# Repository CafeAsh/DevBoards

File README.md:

# Embedded Hardware Design Library

A collection of reusable embedded hardware designs developed as a personal reference library for future electronics and embedded-systems projects.

This repository contains custom development boards, microcontroller platforms, and DC-DC power-conversion designs. The goal is to maintain a structured library of proven circuit designs that can be reused, adapted, and expanded for future projects.

The designs emphasize **practical PCB implementation, component selection, power integrity, signal integrity, manufacturability, and reusable hardware architecture**.

This repository also serves as an ongoing engineering and learning platform. Designs are developed, evaluated, and refined to strengthen practical skills in embedded systems, PCB design, power electronics, signal integrity, and hardware validation. Lessons learned from each design are incorporated into subsequent revisions and projects.

---

## Repository Contents

### Microcontroller Development Boards

| Platform      | MCU                              | Primary Focus                                              |
| ------------- | -------------------------------- | ---------------------------------------------------------- |
| ATtiny1616    | Microchip ATtiny1616             | Low-cost / low-power embedded control                      |
| ATmega32U4    | Microchip ATmega32U4             | USB-capable embedded applications                          |
| ESP32-S3      | Espressif ESP32-S3               | Wi-Fi / Bluetooth / high-performance embedded applications |
| RP2040        | Raspberry Pi RP2040              | Dual-core MCU development                                  |
| STM32F103C8T6 | STMicroelectronics STM32F103C8T6 | ARM Cortex-M3 embedded development                         |

### Power Electronics

The repository also contains several DC-DC converter reference designs:

* Buck converter
* Boost converter
* SEPIC converter

These designs are intended as reusable starting points for future power-supply requirements, with component values and operating parameters selected for their respective target applications.

---

## Design Philosophy

The primary objective of this repository is **reusability**.

Rather than designing every development board or power stage from scratch, commonly used circuits are maintained as modular reference designs that can be incorporated into future projects.

Designs are developed with consideration for:

* Component availability
* PCB manufacturability
* Power distribution
* Decoupling and bypassing
* Signal integrity
* Grounding and return paths
* Programming and debugging interfaces
* Protection circuitry
* Ease of modification and reuse

---

## Development Boards

### ATtiny1616

Reference development board centered around the Microchip ATtiny1616 microcontroller.

Design considerations include:

* USB-to-serial conversion
* Programming/debug interface
* GPIO accessibility
* External power input
* Reset/programming provisions

### ATmega32U4

USB-capable development board based on the ATmega32U4.

The design provides a reusable platform for projects requiring:

* Native USB
* GPIO expansion
* Embedded control
* HID applications
* External peripherals

### ESP32-S3

Development platform based on the ESP32-S3 for projects requiring greater processing capability and wireless connectivity.

The design focuses on providing a reusable hardware platform while accounting for the additional power, RF, and high-speed considerations associated with the device.

### RP2040

Development board based on the Raspberry Pi RP2040.

The design provides a flexible platform for embedded applications requiring:

* Dual-core processing
* High-speed GPIO
* Programmable I/O
* USB connectivity
* External peripheral interfaces

### STM32F103C8T6

ARM Cortex-M3 development platform based on the STM32F103C8T6.

The design provides a compact reference platform for applications requiring:

* ARM Cortex-M development
* General-purpose peripherals
* Multiple communication interfaces
* External debugging/programming

---

## Power Conversion

### Buck Converter

Step-down DC-DC converter designs for applications requiring a regulated output voltage below the input voltage.

Design considerations include:

* Switching frequency
* Inductor selection
* Output capacitance
* MOSFET selection
* Diode or synchronous rectification
* Feedback network
* Switching losses
* Thermal performance
* PCB current paths

### Boost Converter

Step-up DC-DC converter designs for generating an output voltage greater than the input voltage.

Key considerations include:

* Inductor selection
* Switching device selection
* Diode characteristics
* Output ripple
* Duty-cycle limitations
* Feedback and regulation
* Current requirements

### SEPIC Converter

Single-Ended Primary-Inductor Converter designs for applications requiring an output voltage that may be either above or below the input voltage.

SEPIC designs are particularly useful when the input voltage can cross the desired output voltage while maintaining a non-inverting regulated output.

---

## Design Documentation

Each design is intended to become increasingly self-documenting as the repository develops.

Where applicable, documentation will include:

* Design objectives
* Electrical specifications
* Schematic
* PCB layout
* Bill of materials
* Component selection rationale
* Design calculations
* Simulation results
* PCB fabrication files
* Assembly information
* Bring-up and validation notes
* Known limitations
* Revision history

Measured results will be distinguished from simulated or calculated values.

---

## Tools

The designs in this repository may utilize:

* **KiCad** — Schematic capture and PCB design
* **LTspice** — Circuit simulation
* **Datasheet analysis** — Component selection and electrical verification
* **Embedded development tools** — Firmware development and hardware bring-up

Additional tools may be added as the library expands.

---

## Future Development

Planned additions and improvements include:

* Additional MCU development boards
* Expanded DC-DC converter library
* Reusable power-entry circuits
* USB interface designs
* Debug/programming interfaces
* ESD and transient protection circuits
* Load-switch and power-management circuits

---

## Status

This repository is an actively evolving engineering reference library.

Designs should be considered **development/reference hardware unless explicitly marked as validated**. Electrical specifications, component selections, and layouts may change as designs are tested and refined.

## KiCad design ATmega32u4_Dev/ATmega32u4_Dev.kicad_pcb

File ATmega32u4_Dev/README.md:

# ATmega32U4 Development Board

Development board based on the **ATmega32U4** microcontroller, designed for USB-enabled embedded projects, rapid prototyping, and firmware experimentation.

## Overview

This project provides a hardware platform built around the ATmega32U4, a microcontroller with native USB support.

Ideal use cases include:

* USB HID devices (keyboards, mice, gamepads)
* Serial communication over USB (CDC)
* Custom USB devices
* General embedded applications

## Features

* ATmega32U4 microcontroller
* Native USB support (no external USB-to-UART chip required)
* On-board 5V voltage regulation
* Power and Dataline surge protection
* ISP programming header
* Power Status LED
* Programable on board LED (Pin 13)
* GPIO breakout pins
* 16MHz Crystal Oscillator
* Designed to fit standard breadboards

## Microcontroller Details

* **Core:** AVR 8-bit
* **Flash Memory:** 32 KB
* **SRAM:** 2.5 KB
* **EEPROM:** 1 KB
* **Clock Speed:**  16 MHz
* **Interfaces:**
  * USB 2.0 Full Speed
  * UART
  * SPI
  * I2C (TWI)

## Pinout

*Pinout leaves some to be desired. Future re-works will better address pin layout*

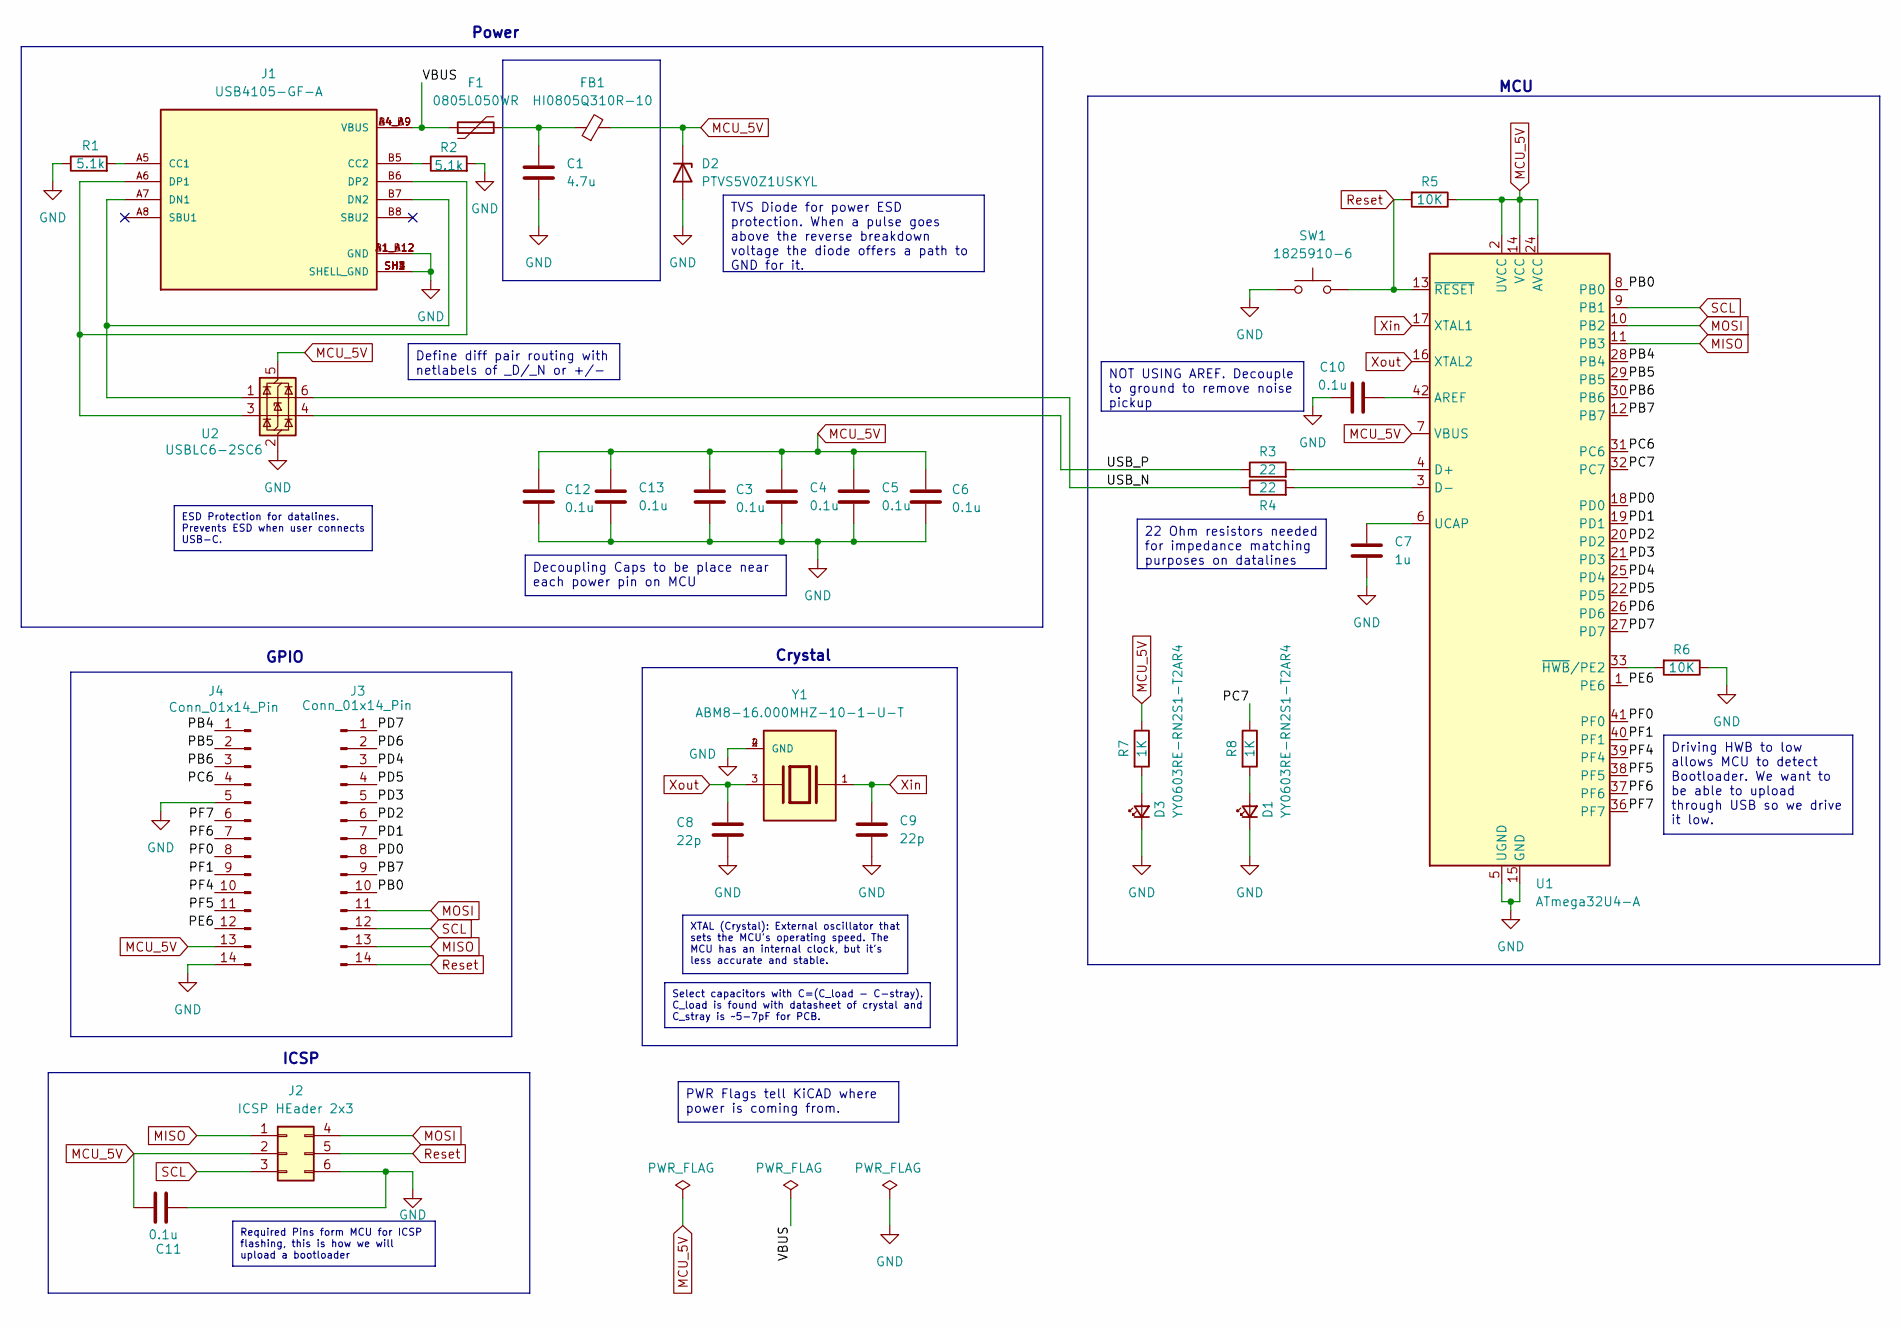
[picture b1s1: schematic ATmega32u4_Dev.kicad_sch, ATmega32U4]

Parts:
C1: 4.7u; C_0402_1005Metric
C3, C4, C5, C6, C10, C11, C12, C13: 0.1u; C_0402_1005Metric
C7: 1u; C_0402_1005Metric
C8, C9: 22p; C_0402_1005Metric
D1, D3: YY0603RE-RN2S1-T2AR4; LED_0603_1608Metric
D2: PTVS5V0Z1USKYL; Nexperia_DSN1608-2_1.6x0.8mm
F1: 0805L050WR; Fuse_0805_2012Metric_Pad1.15x1.40mm_HandSolder
FB1: HI0805Q310R-10; L_0805_2012Metric_Pad1.05x1.20mm_HandSolder
J1: USB4105-GF-A; GCT_USB4105-GF-A; PARTREV B4
J2: ICSP HEader 2x3; 02x03 Header
J3, J4: Conn_01x14_Pin; 01x14 Header (2.54 Pitch)
R1, R2: 5.1k; R_0402_1005Metric
R3, R4: 22; R_0402_1005Metric
R5, R6: 10K; R_0402_1005Metric
R7, R8: 1K; R_0402_1005Metric
SW1: 1825910-6; Generic SW 3x4mm
U1: ATmega32U4-A; QFP80P1200X1200X120-44N
U2: USBLC6-2SC6; SOT-23-6
Y1: ABM8-16.000MHZ-10-1-U-T; XTAL_ABM8-16.000MHZ-10-1-U-T; PARTREV 44041

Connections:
/PB0: J3.10, U1.8 (PB0)
/PB4: J4.1, U1.28 (PB4)
/PB5: J4.2, U1.29 (PB5)
/PB6: J4.3, U1.30 (PB6)
/PB7: J3.9, U1.12 (PB7)
/PC6: J4.4, U1.31 (PC6)
/PC7: R8.1, U1.32 (PC7)
/PD0: J3.8, U1.18 (PD0)
/PD1: J3.7, U1.19 (PD1)
/PD2: J3.6, U1.20 (PD2)
/PD3: J3.5, U1.21 (PD3)
/PD4: J3.3, U1.25 (PD4)
/PD5: J3.4, U1.22 (PD5)
/PD6: J3.2, U1.26 (PD6)
/PD7: J3.1, U1.27 (PD7)
/PE6: J4.12, U1.1 (PE6)
/PF0: J4.8, U1.41 (PF0)
/PF1: J4.9, U1.40 (PF1)
/PF4: J4.10, U1.39 (PF4)
/PF5: J4.11, U1.38 (PF5)
/PF6: J4.7, U1.37 (PF6)
/PF7: J4.6, U1.36 (PF7)
/USB_N: R4.1, U2.6 (I/O1)
/USB_P: R3.1, U2.4 (I/O2)
/VBUS: F1.1, J1.A4_B9 (VBUS), J1.B4_A9 (VBUS)
GND: C1.2, C3.2, C4.2, C5.2, C6.2, C7.2, C8.2, C9.2, C10.1, C11.2, C12.2, C13.2, D1.1 (K), D2.2 (A), D3.1 (K), J1.A1_B12 (GND), J1.B1_A12 (GND), J1.SH1 (SHELL_GND), J1.SH2 (SHELL_GND), J1.SH3 (SHELL_GND), J1.SH4 (SHELL_GND), J2.6, J4.5, J4.14, R1.1, R2.2, R6.1, SW1.1, U1.5 (UGND), U1.15 (GND), U1.23 (GND), U1.35 (GND), U1.43 (GND), U2.2 (GND), Y1.2 (GND), Y1.4 (GND)
MCU_5V: C3.1, C4.1, C5.1, C6.1, C11.1, C12.1, C13.1, D2.1 (K), FB1.2, J2.2, J4.13, R5.1, R7.1, U1.2 (UVCC), U1.7 (VBUS), U1.14 (VCC), U1.24 (AVCC), U1.34 (VCC), U1.44 (AVCC), U2.5 (VBUS)
MISO: J2.1, J3.13, U1.11 (PB3)
MOSI: J2.4, J3.11, U1.10 (PB2)
unnamed: C1.1, F1.2, FB1.1
unnamed: D1.2 (A), R8.2
unnamed: D3.2 (A), R7.2
unnamed: J1.A5 (CC1), R1.2
unnamed: J1.B5 (CC2), R2.1
unnamed: J1.A7 (DN1), J1.B7 (DN2), U2.1 (I/O1)
unnamed: J1.A6 (DP1), J1.B6 (DP2), U2.3 (I/O2)
unnamed: C10.2, U1.42 (AREF)
unnamed: R3.2, U1.4 (D+)
unnamed: R4.2, U1.3 (D-)
unnamed: C7.1, U1.6 (UCAP)
unnamed: R6.2, U1.33 (~HWB/PE2)
Reset: J2.5, J3.14, R5.2, SW1.2, U1.13 (~RESET)
SCL: J2.3, J3.12, U1.9 (PB1)
Xin: C9.1, U1.17 (XTAL1), Y1.1
Xout: C8.1, U1.16 (XTAL2), Y1.3

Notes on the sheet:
MCU
GPIO
Crystal
ICSP
Power
Driving HWB to low allows MCU to detect Bootloader. We want to be able to upload through USB so we drive it low.
NOT USING AREF. Decouple to ground to remove noise pickup
PWR Flags tell KiCAD where power is coming from.
ESD Protection for datalines. Prevents ESD when user connects USB-C.
TVS Diode for power ESD protection. When a pulse goes above the reverse breakdown voltage the diode offers a path to GND for it.
22 Ohm resistors needed for impedance matching purposes on datalines
Required Pins form MCU for ICSP flashing, this is how we will upload a bootloader
Decoupling Caps to be place near each power pin on MCU
XTAL (Crystal): External oscillator that sets the MCU's operating speed. The MCU has an internal clock, but it's less accurate and stable.
Select capacitors with C=(C_load - C-stray). C_load is found with datasheet of crystal and C_stray is ~5-7pF for PCB.
Define diff pair routing with netlabels of _D/_N or +/-

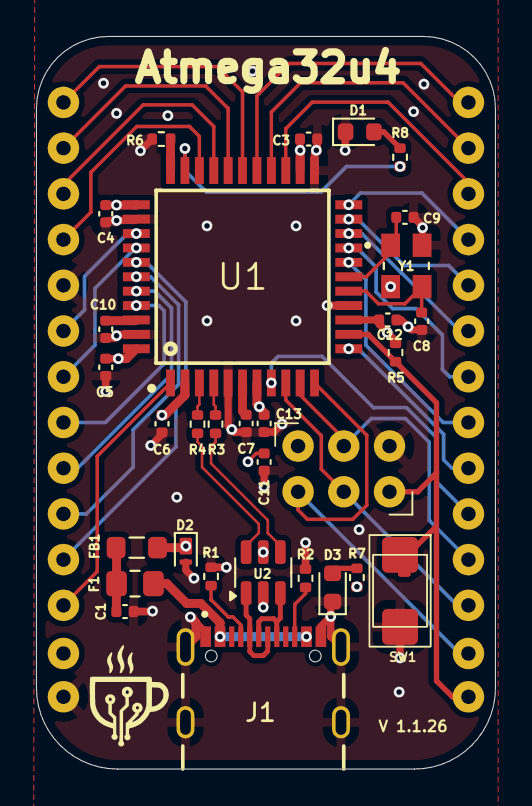
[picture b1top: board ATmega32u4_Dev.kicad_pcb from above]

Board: 4 copper layers, 25.5 x 40.7 mm, 33 parts (0 on the bottom side), 45 nets.

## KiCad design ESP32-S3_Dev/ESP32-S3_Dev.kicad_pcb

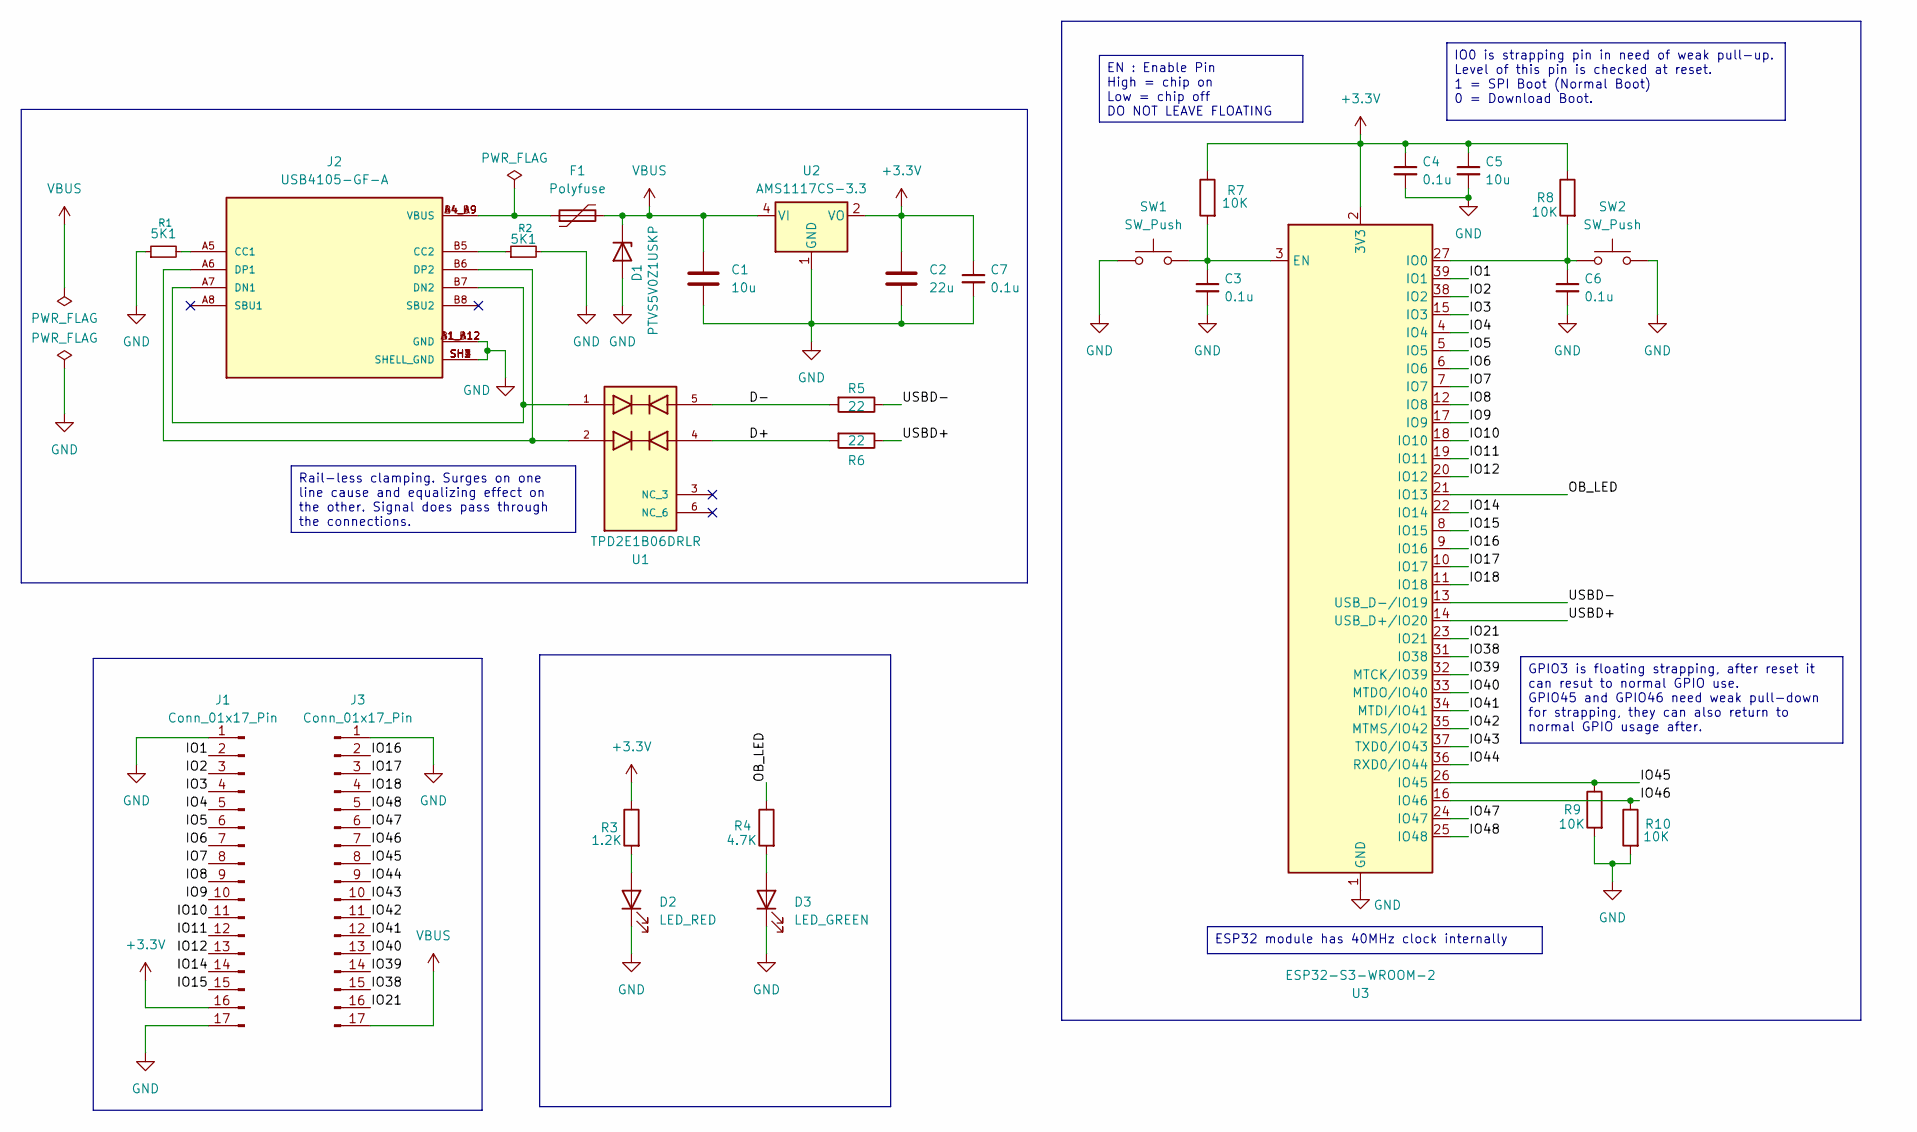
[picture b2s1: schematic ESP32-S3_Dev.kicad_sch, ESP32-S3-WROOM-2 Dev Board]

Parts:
C1, C5: 10u; C_0402_1005Metric
C2: 22u; C_0402_1005Metric
C3, C4, C6, C7: 0.1u; C_0402_1005Metric
D1: PTVS5V0Z1USKP; Nexperia_DSN1608-2_1.6x0.8mm
D2: LED_RED; LED_0603_1608Metric
D3: LED_GREEN; LED_0603_1608Metric
F1: Polyfuse; Fuse_0603_1608Metric
J1, J3: Conn_01x17_Pin; PinHeader_1x17_P2.54mm_Vertical
J2: USB4105-GF-A; USB_C_Receptacle_GCT_USB4105-xx-A_16P_TopMnt_Horizontal; PARTREV B4
R1, R2: 5K1; R_0402_1005Metric
R3: 1.2K; R_0402_1005Metric
R4: 4.7K; R_0402_1005Metric
R5, R6: 22; R_0402_1005Metric
R7, R8, R9, R10: 10K; R_0402_1005Metric
SW1, SW2: SW_Push; R_0402_1005Metric
U1: TPD2E1B06DRLR; SOTFL50P160X60-6N; PARTREV D
U2: AMS1117CS-3.3; SOIC-8_3.9x4.9mm_P1.27mm
U3: ESP32-S3-WROOM-2

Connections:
+3.3V: C2.1, C4.1, C5.1, C7.1, J1.16, R3.1, R7.1, R8.1, U2.2 (VO), U2.3 (VO), U2.6 (VO), U2.7 (VO), U3.2 (3V3)
/D+: R6.2, U1.4
/D-: R5.2, U1.5
/IO1: J1.2, U3.39 (IO1)
/IO2: J1.3, U3.38 (IO2)
/IO3: J1.4, U3.15 (IO3)
/IO4: J1.5, U3.4 (IO4)
/IO5: J1.6, U3.5 (IO5)
/IO6: J1.7, U3.6 (IO6)
/IO7: J1.8, U3.7 (IO7)
/IO8: J1.9, U3.12 (IO8)
/IO9: J1.10, U3.17 (IO9)
/IO10: J1.11, U3.18 (IO10)
/IO11: J1.12, U3.19 (IO11)
/IO12: J1.13, U3.20 (IO12)
/IO14: J1.14, U3.22 (IO14)
/IO15: J1.15, U3.8 (IO15)
/IO16: J3.2, U3.9 (IO16)
/IO17: J3.3, U3.10 (IO17)
/IO18: J3.4, U3.11 (IO18)
/IO21: J3.16, U3.23 (IO21)
/IO38: J3.15, U3.31 (IO38)
/IO39: J3.14, U3.32 (MTCK/IO39)
/IO40: J3.13, U3.33 (MTDO/IO40)
/IO41: J3.12, U3.34 (MTDI/IO41)
/IO42: J3.11, U3.35 (MTMS/IO42)
/IO43: J3.10, U3.37 (TXD0/IO43)
/IO44: J3.9, U3.36 (RXD0/IO44)
/IO45: J3.8, R9.1, U3.26 (IO45)
/IO46: J3.7, R10.1, U3.16 (IO46)
/IO47: J3.6, U3.24 (IO47)
/IO48: J3.5, U3.25 (IO48)
/OB_LED: R4.1, U3.21 (IO13)
/USBD+: R6.1, U3.14 (USB_D+/IO20)
/USBD-: R5.1, U3.13 (USB_D-/IO19)
GND: C1.2, C2.2, C3.2, C4.2, C5.2, C6.2, C7.2, D1.2 (A), D2.1 (K), D3.1 (K), J1.1, J1.17, J2.A1_B12 (GND), J2.B1_A12 (GND), J2.SH1 (SHELL_GND), J2.SH2 (SHELL_GND), J2.SH3 (SHELL_GND), J2.SH4 (SHELL_GND), J3.1, R1.1, R2.2, R9.2, R10.2, SW1.1, SW2.2, U2.1 (GND), U3.1 (GND), U3.40 (GND), U3.41 (GND)
unnamed: D2.2 (A), R3.2
unnamed: D3.2 (A), R4.2
unnamed: F1.1, J2.A4_B9 (VBUS), J2.B4_A9 (VBUS)
unnamed: J2.A5 (CC1), R1.2
unnamed: J2.B5 (CC2), R2.1
unnamed: J2.A7 (DN1), J2.B7 (DN2), U1.1
unnamed: J2.A6 (DP1), J2.B6 (DP2), U1.2
unnamed: C3.1, R7.2, SW1.2, U3.3 (EN)
unnamed: C6.1, R8.2, SW2.1, U3.27 (IO0)
VBUS: C1.1, D1.1 (K), F1.2, J3.17, U2.4 (VI)

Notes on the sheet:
Rail-less clamping. Surges on one line cause and equalizing effect on the other. Signal does pass through the connections.
EN : Enable Pin High = chip on Low = chip off DO NOT LEAVE FLOATING
GPIO3 is floating strapping, after reset it can resut to normal GPIO use. GPIO45 and GPIO46 need weak pull-down for strapping, they can also return to normal GPIO usage after.
ESP32 module has 40MHz clock internally
IO0 is strapping pin in need of weak pull-up. Level of this pin is checked at reset. 1 = SPI Boot (Normal Boot) 0 = Download Boot.

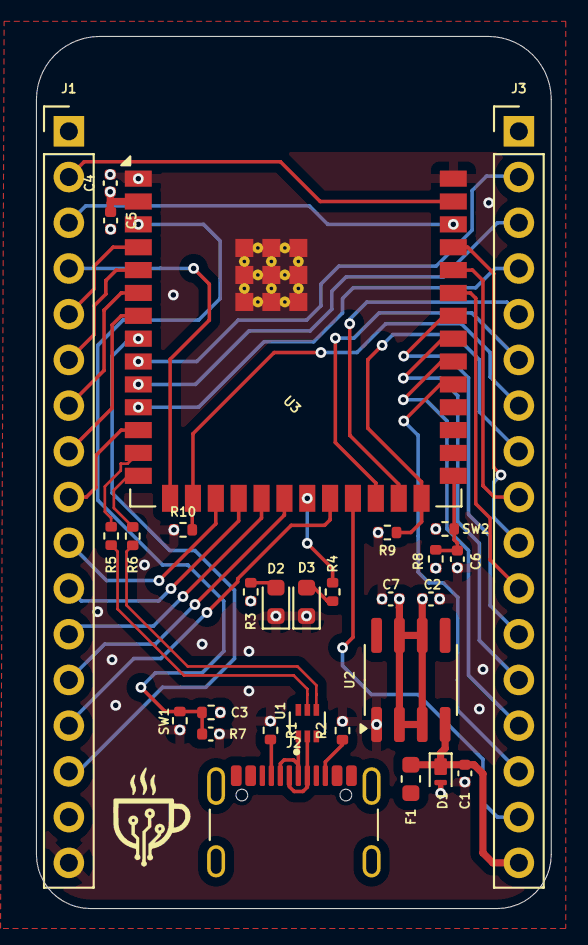
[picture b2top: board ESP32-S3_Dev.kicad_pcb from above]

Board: 4 copper layers, 28.6 x 48.5 mm, 29 parts (0 on the bottom side), 45 nets.

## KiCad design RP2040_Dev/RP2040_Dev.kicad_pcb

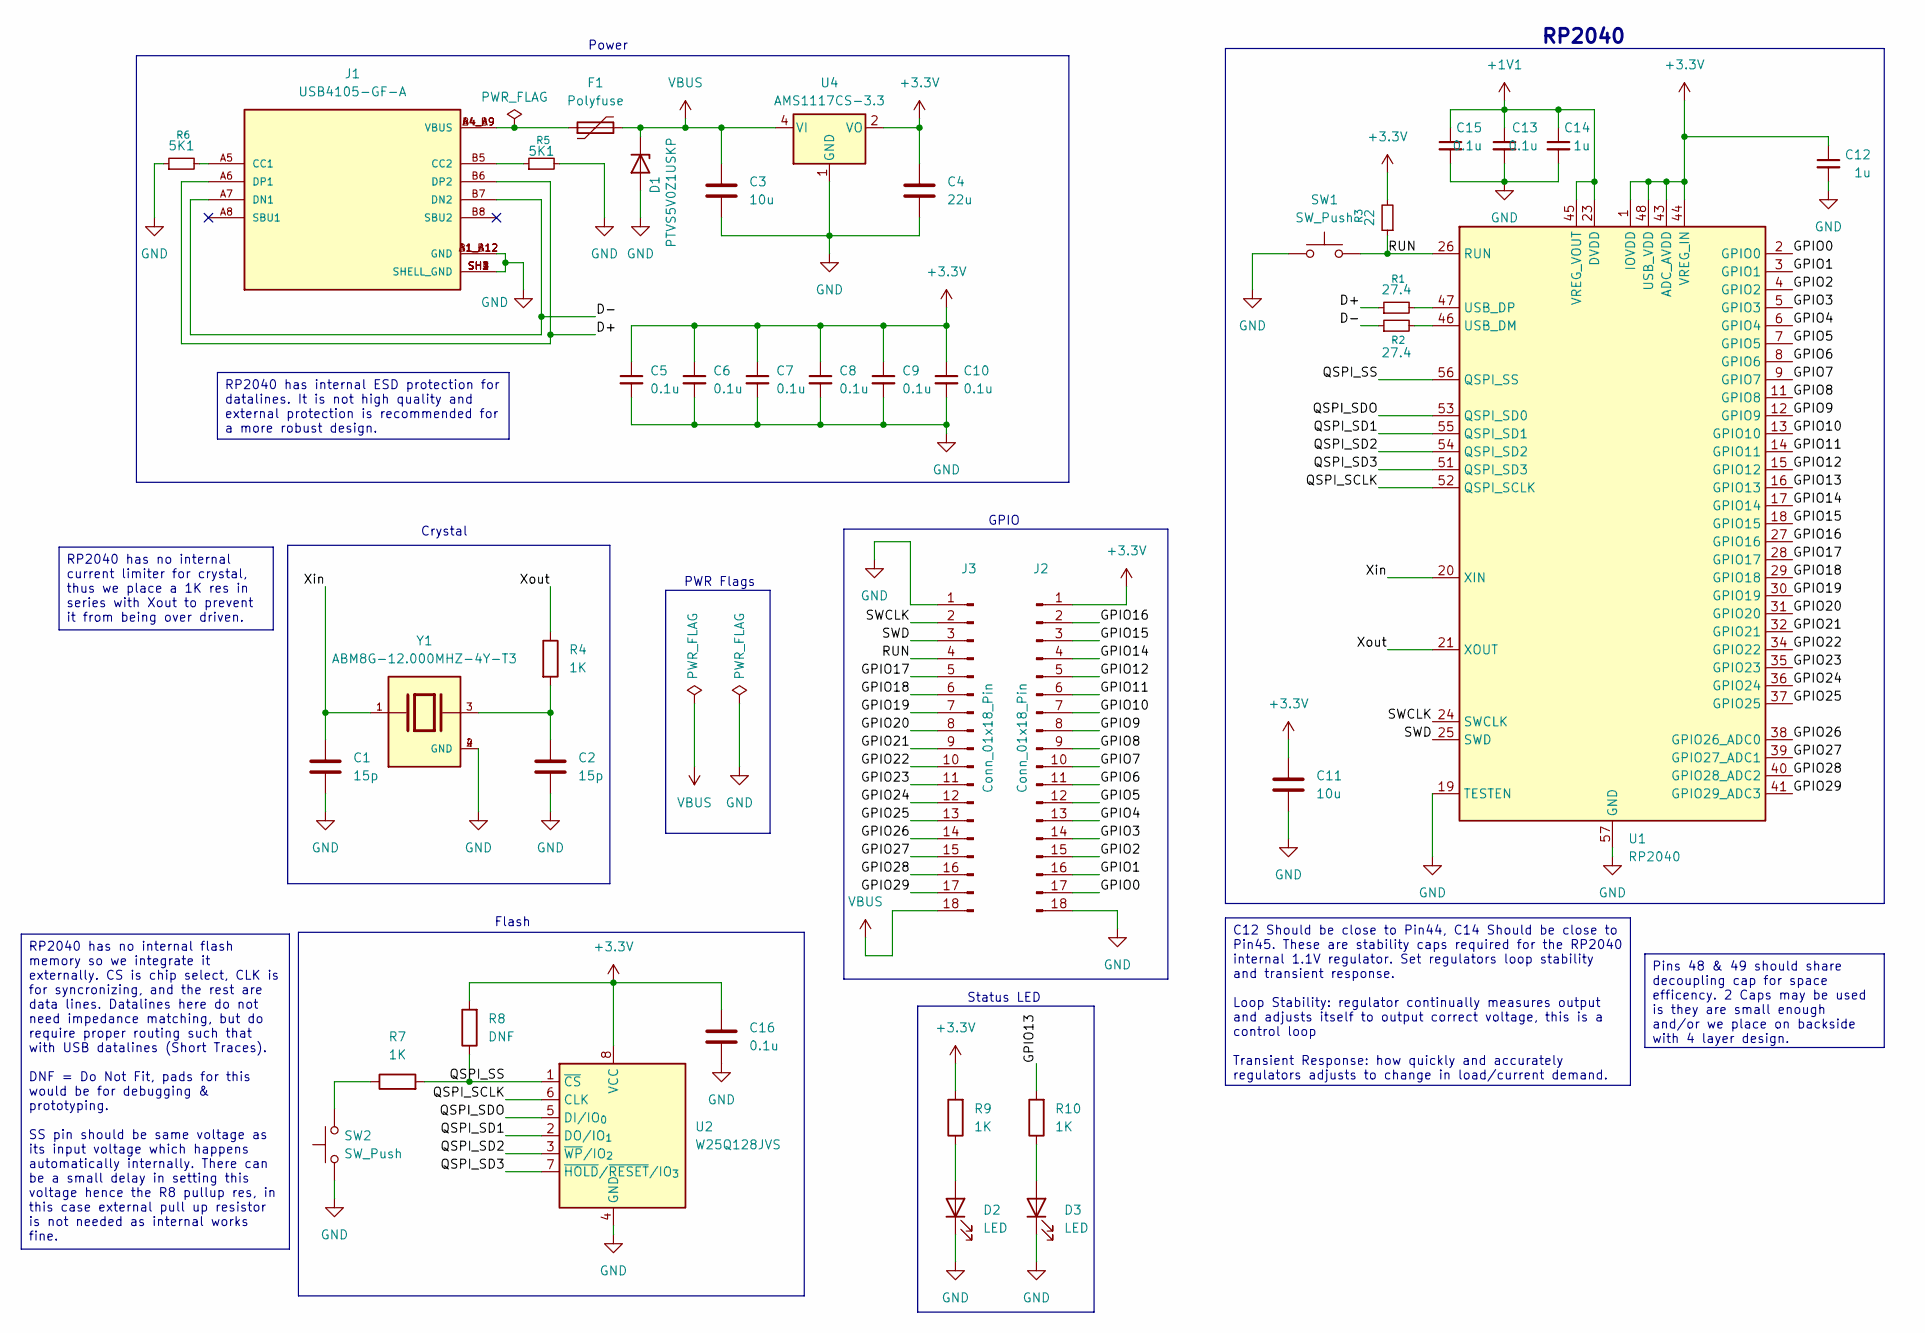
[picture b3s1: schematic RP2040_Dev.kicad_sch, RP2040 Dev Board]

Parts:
C1, C2: 15p; C_0402_1005Metric
C3, C11: 10u; C_0402_1005Metric
C4: 22u; C_0402_1005Metric
C5, C6, C7, C8, C9, C10, C13, C15, C16: 0.1u; C_0402_1005Metric
C12, C14: 1u; C_0402_1005Metric
D1: PTVS5V0Z1USKP; Nexperia_DSN1608-2_1.6x0.8mm
D2, D3: LED; LED_0603_1608Metric_Pad1.05x0.95mm_HandSolder
F1: Polyfuse; Fuse_0603_1608Metric
J1: USB4105-GF-A; GCT_USB4105-GF-A; PARTREV B4
J2, J3: Conn_01x18_Pin; PinHeader_1x18_P2.54mm_Vertical
R1, R2: 27.4; R_0201_0603Metric_Pad0.64x0.40mm_HandSolder
R3: 22; R_0201_0603Metric_Pad0.64x0.40mm_HandSolder
R4: 1K; R_0201_0603Metric_Pad0.64x0.40mm_HandSolder
R5, R6: 5K1; R_0201_0603Metric_Pad0.64x0.40mm_HandSolder
R7, R9, R10: 1K; R_0402_1005Metric
R8: DNF; R_0402_1005Metric
SW1, SW2: SW_Push; L_0805_2012Metric_Pad1.05x1.20mm_HandSolder
U1: RP2040; QFN-56-1EP_7x7mm_P0.4mm_EP3.2x3.2mm
U2: W25Q128JVS; SOIC-8_5.3x5.3mm_P1.27mm
U4: AMS1117CS-3.3; SOIC-8_3.9x4.9mm_P1.27mm
Y1: ABM8G-12.000MHZ-4Y-T3; XTAL_ABM8G-12.000MHZ-4Y-T3; PARTREV 08.13.15

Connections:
+1V1: C13.1, C14.1, C15.1, U1.23 (DVDD), U1.45 (VREG_VOUT), U1.50 (DVDD)
+3.3V: C4.1, C5.1, C6.1, C7.1, C8.1, C9.1, C10.1, C11.1, C12.1, C16.1, J2.1, R3.2, R8.2, R9.2, U1.1 (IOVDD), U1.10 (IOVDD), U1.22 (IOVDD), U1.33 (IOVDD), U1.42 (IOVDD), U1.43 (ADC_AVDD), U1.44 (VREG_IN), U1.48 (USB_VDD), U1.49 (IOVDD), U2.8 (VCC), U4.2 (VO), U4.3 (VO), U4.6 (VO), U4.7 (VO)
/D+: J1.A6 (DP1), J1.B6 (DP2), R1.1
/D-: J1.A7 (DN1), J1.B7 (DN2), R2.1
/GPIO0: J2.17, U1.2 (GPIO0)
/GPIO1: J2.16, U1.3 (GPIO1)
/GPIO2: J2.15, U1.4 (GPIO2)
/GPIO3: J2.14, U1.5 (GPIO3)
/GPIO4: J2.13, U1.6 (GPIO4)
/GPIO5: J2.12, U1.7 (GPIO5)
/GPIO6: J2.11, U1.8 (GPIO6)
/GPIO7: J2.10, U1.9 (GPIO7)
/GPIO8: J2.9, U1.11 (GPIO8)
/GPIO9: J2.8, U1.12 (GPIO9)
/GPIO10: J2.7, U1.13 (GPIO10)
/GPIO11: J2.6, U1.14 (GPIO11)
/GPIO12: J2.5, U1.15 (GPIO12)
/GPIO13: R10.2, U1.16 (GPIO13)
/GPIO14: J2.4, U1.17 (GPIO14)
/GPIO15: J2.3, U1.18 (GPIO15)
/GPIO16: J2.2, U1.27 (GPIO16)
/GPIO17: J3.5, U1.28 (GPIO17)
/GPIO18: J3.6, U1.29 (GPIO18)
/GPIO19: J3.7, U1.30 (GPIO19)
/GPIO20: J3.8, U1.31 (GPIO20)
/GPIO21: J3.9, U1.32 (GPIO21)
/GPIO22: J3.10, U1.34 (GPIO22)
/GPIO23: J3.11, U1.35 (GPIO23)
/GPIO24: J3.12, U1.36 (GPIO24)
/GPIO25: J3.13, U1.37 (GPIO25)
/GPIO26: J3.14, U1.38 (GPIO26_ADC0)
/GPIO27: J3.15, U1.39 (GPIO27_ADC1)
/GPIO28: J3.16, U1.40 (GPIO28_ADC2)
/GPIO29: J3.17, U1.41 (GPIO29_ADC3)
/QSPI_SCLK: U1.52 (QSPI_SCLK), U2.6 (CLK)
/QSPI_SD1: U1.55 (QSPI_SD1), U2.2 (DO/IO_{1})
/QSPI_SD2: U1.54 (QSPI_SD2), U2.3 (~WP/IO_{2})
/QSPI_SD3: U1.51 (QSPI_SD3), U2.7 (~HOLD/~RESET/IO_{3})
/QSPI_SDO: U1.53 (QSPI_SD0), U2.5 (DI/IO_{0})
/QSPI_SS: R7.2, R8.1, U1.56 (QSPI_SS), U2.1 (~CS)
/RUN: J3.4, R3.1, SW1.2, U1.26 (RUN)
/SWCLK: J3.2, U1.24 (SWCLK)
/SWD: J3.3, U1.25 (SWD)
/Xin: C1.1, U1.20 (XIN), Y1.1
/Xout: R4.1, U1.21 (XOUT)
GND: C1.2, C2.2, C3.2, C4.2, C5.2, C6.2, C7.2, C8.2, C9.2, C10.2, C11.2, C12.2, C13.2, C14.2, C15.2, C16.2, D1.2 (A), D2.1 (K), D3.1 (K), J1.A1_B12 (GND), J1.B1_A12 (GND), J1.SH1 (SHELL_GND), J1.SH2 (SHELL_GND), J1.SH3 (SHELL_GND), J1.SH4 (SHELL_GND), J2.18, J3.1, R5.2, R6.1, SW1.1, SW2.1, U1.19 (TESTEN), U1.57 (GND), U2.4 (GND), U4.1 (GND), Y1.2 (GND), Y1.4 (GND)
unnamed: C2.1, R4.2, Y1.3
unnamed: D2.2 (A), R9.1
unnamed: D3.2 (A), R10.1
unnamed: F1.1, J1.A4_B9 (VBUS), J1.B4_A9 (VBUS)
unnamed: J1.A5 (CC1), R6.2
unnamed: J1.B5 (CC2), R5.1
unnamed: R7.1, SW2.2
unnamed: R2.2, U1.46 (USB_DM)
unnamed: R1.2, U1.47 (USB_DP)
VBUS: C3.1, D1.1 (K), F1.2, J3.18, U4.4 (VI)

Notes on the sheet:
Crystal
GPIO
Status LED
RP2040
Flash
Power
PWR Flags
RP2040 has no internal flash memory so we integrate it externally. CS is chip select, CLK is for syncronizing, and the rest are data lines. Datalines here do not need impedance matching, but do require proper routing such that with USB datalines (Short Traces). DNF = Do Not Fit, pads for this would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
RP2040 has internal ESD protection for datalines. It is not high quality and external protection is recommended for a more robust design.
C12 Should be close to Pin44, C14 Should be close to Pin45. These are stability caps required for the RP2040 internal 1.1V regulator. Set regulators loop stability and transient response. Loop Stability: regulator continually measures output and adjusts itself to output correct voltage, this is a c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
Pins 48 & 49 should share decoupling cap for space efficency. 2 Caps may be used is they are small enough and/or we place on backside with 4 layer design.
RP2040 has no internal current limiter for crystal, thus we place a 1K res in series with Xout to prevent it from being over driven.

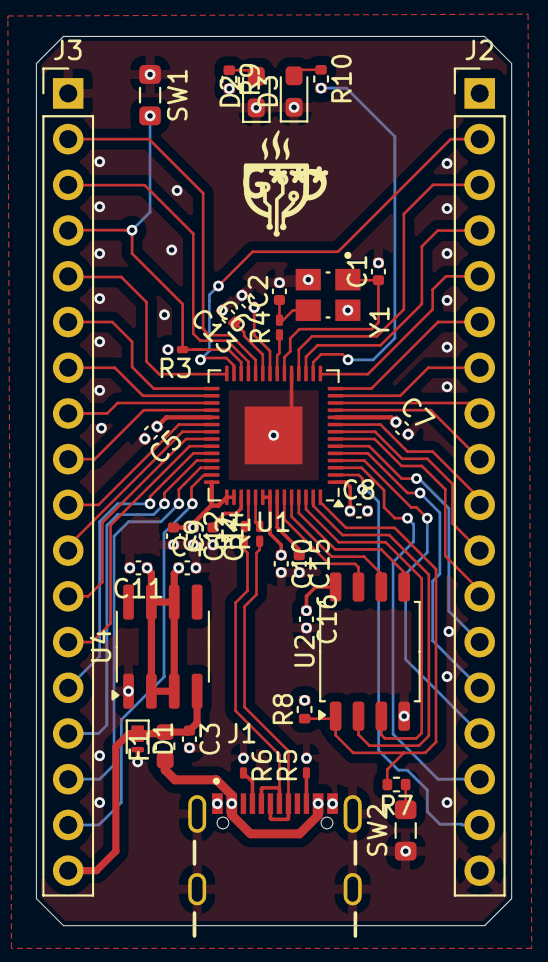
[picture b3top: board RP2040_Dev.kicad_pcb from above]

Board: 4 copper layers, 26.4 x 49.4 mm, 39 parts (0 on the bottom side), 56 nets.

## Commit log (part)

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2025-11-17 intitial commit
2025-11-18 changed GPIO
2025-11-19 Adjusted Layout
2025-11-30 4-layer Atmega and RP2040
2025-12-04 rp2040 update
2025-12-09 Final Atmega32u4
2025-12-31 Adjusted Headers on ATmega32
2026-04-13 Cleaned up atmega and made atmega32 README
2026-04-13 Adjusted Markdown Images
2026-05-10 Added additional board folders, updataed RP2040, ATmega, and ESP32
2026-05-18 Some changes to attiny
2026-05-29 Voltage Converters
